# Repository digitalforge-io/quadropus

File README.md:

# quadropus
quadropus - USB to quad UART bridge

PDF Schematic. The Repository also contains the KiCAD (5.1.9) Files.

[Schematics](/assets/quadropus_schematics_v1.3.pdf)

A picture of the bare PCB. 1.6mm blue Soldermask, Gold ENIG.

This is the optional 3D printed baseplate. You can find the STL and FreeCad Files in the assets directory.

Licensed under:

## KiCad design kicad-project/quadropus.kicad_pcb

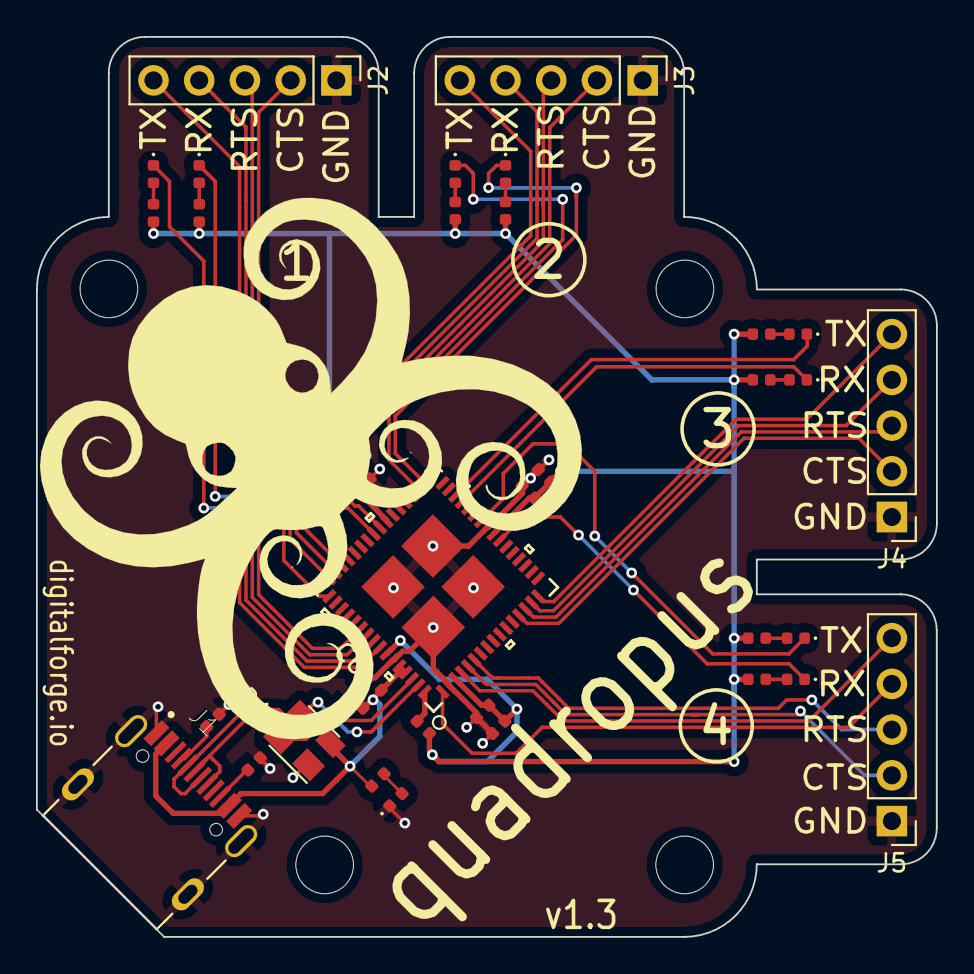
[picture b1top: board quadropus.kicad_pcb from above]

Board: 2 copper layers, 50.0 x 50.0 mm, 42 parts (1 on the bottom side), 41 nets.

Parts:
C1, C2, C5, C6: 0.1uF; C_0402_1005Metric
C3, C4, C7, C8: 4.7uF; C_0402_1005Metric
D1: SP0503BAHTG; SOT-143
D2, D3, D4, D5, D10: GREEN; LED_0402_1005Metric
D6, D7, D8, D9: Orange; LED_0402_1005Metric
H1, H2, H3, H4: MountingHole; MountingHole_3.2mm_M3
J1: USB-C_HRO_31-M-12; HRO_USB-C-31-M-12
J2, J3, J4, J5: Conn_01x05; PinHeader_1x05_P2.54mm_Vertical
LOGO1, LOGO1#2: quadropus
R1, R2: 5.1k; R_0402_1005Metric
R3, R4, R5, R6, R8, R9, R10, R11, R12: 470R; R_0402_1005Metric
R7: 4.7k; R_0402_1005Metric
U1: CP2108-B03-GM

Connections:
/CC1: J1.A5, R1.1
/CC2: J1.B5, R2.1
/CTS0: J2.2, U1.54
/CTS1: J3.2, U1.46
/CTS2: J4.2, U1.13
/CTS3: J5.2, U1.5
/GPIO_0: D6.1, U1.41
/GPIO_1: D2.1, U1.40
/GPIO_4: D7.1, U1.34
/GPIO_5: D3.1, U1.33
/GPIO_8: D8.1, U1.30
/GPIO_9: D4.1, U1.29
/GPIO_12: D9.1, U1.26
/GPIO_13: D5.1, U1.23
/RTS0: J2.3, U1.55
/RTS1: J3.3, U1.47
/RTS2: J4.3, U1.14
/RTS3: J5.3, U1.6
/RX0: J2.4, U1.56
/RX1: J3.4, U1.48
/RX2: J4.4, U1.15
/RX3: J5.4, U1.1
/TX0: J2.5, U1.57
/TX1: J3.5, U1.49
/TX2: J4.5, U1.16
/TX3: J5.5, U1.4
/USBD+: D1.4, J1.A6, J1.B6, U1.62
/USBD-: D1.3, J1.A7, J1.B7, U1.63
GND: C1.2, C2.2, C3.2, C4.2, C5.2, C6.2, C7.2, C8.2, D1.1, D10.1, J1.A1B12, J1.B1A12, J1.S1, J1.S2, J1.S3, J1.S4, J2.1, J3.1, J4.1, J5.1, R1.2, R2.2, U1.2, U1.25, U1.59, U1.65
unnamed: D2.2, R3.2
unnamed: D3.2, R4.2
unnamed: D4.2, R5.2
unnamed: D5.2, R6.2
unnamed: D6.2, R8.2
unnamed: D7.2, R9.2
unnamed: D8.2, R10.2
unnamed: D9.2, R11.2
unnamed: D10.2, R12.2
unnamed: R7.2, U1.64
VBUS: C6.1, C8.1, D1.2, J1.A4B9, J1.B4A9, R12.1, U1.60, U1.61
VDD: C1.1, C2.1, C3.1, C4.1, C5.1, C7.1, R3.1, R4.1, R5.1, R6.1, R7.1, R8.1, R9.1, R10.1, R11.1, U1.3, U1.24, U1.39, U1.58

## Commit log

2021-04-15 final upload to GH
2021-04-15 added DS & schematics PDF
2021-04-15 README and assets
2021-04-15 added baseplate STL & FreeCad Files
2021-04-15 starting GH pages Docu
2021-04-15 Set theme jekyll-theme-minimal
2021-04-15 update doc
2021-04-15 docs
2021-04-15 Update Gemfile
2021-04-18 rm docs
2021-05-16 Swap TX/RX LEDs

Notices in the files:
parts and their libraries:
Copyright 2016 Accelerated Designs. All rights reserved.
